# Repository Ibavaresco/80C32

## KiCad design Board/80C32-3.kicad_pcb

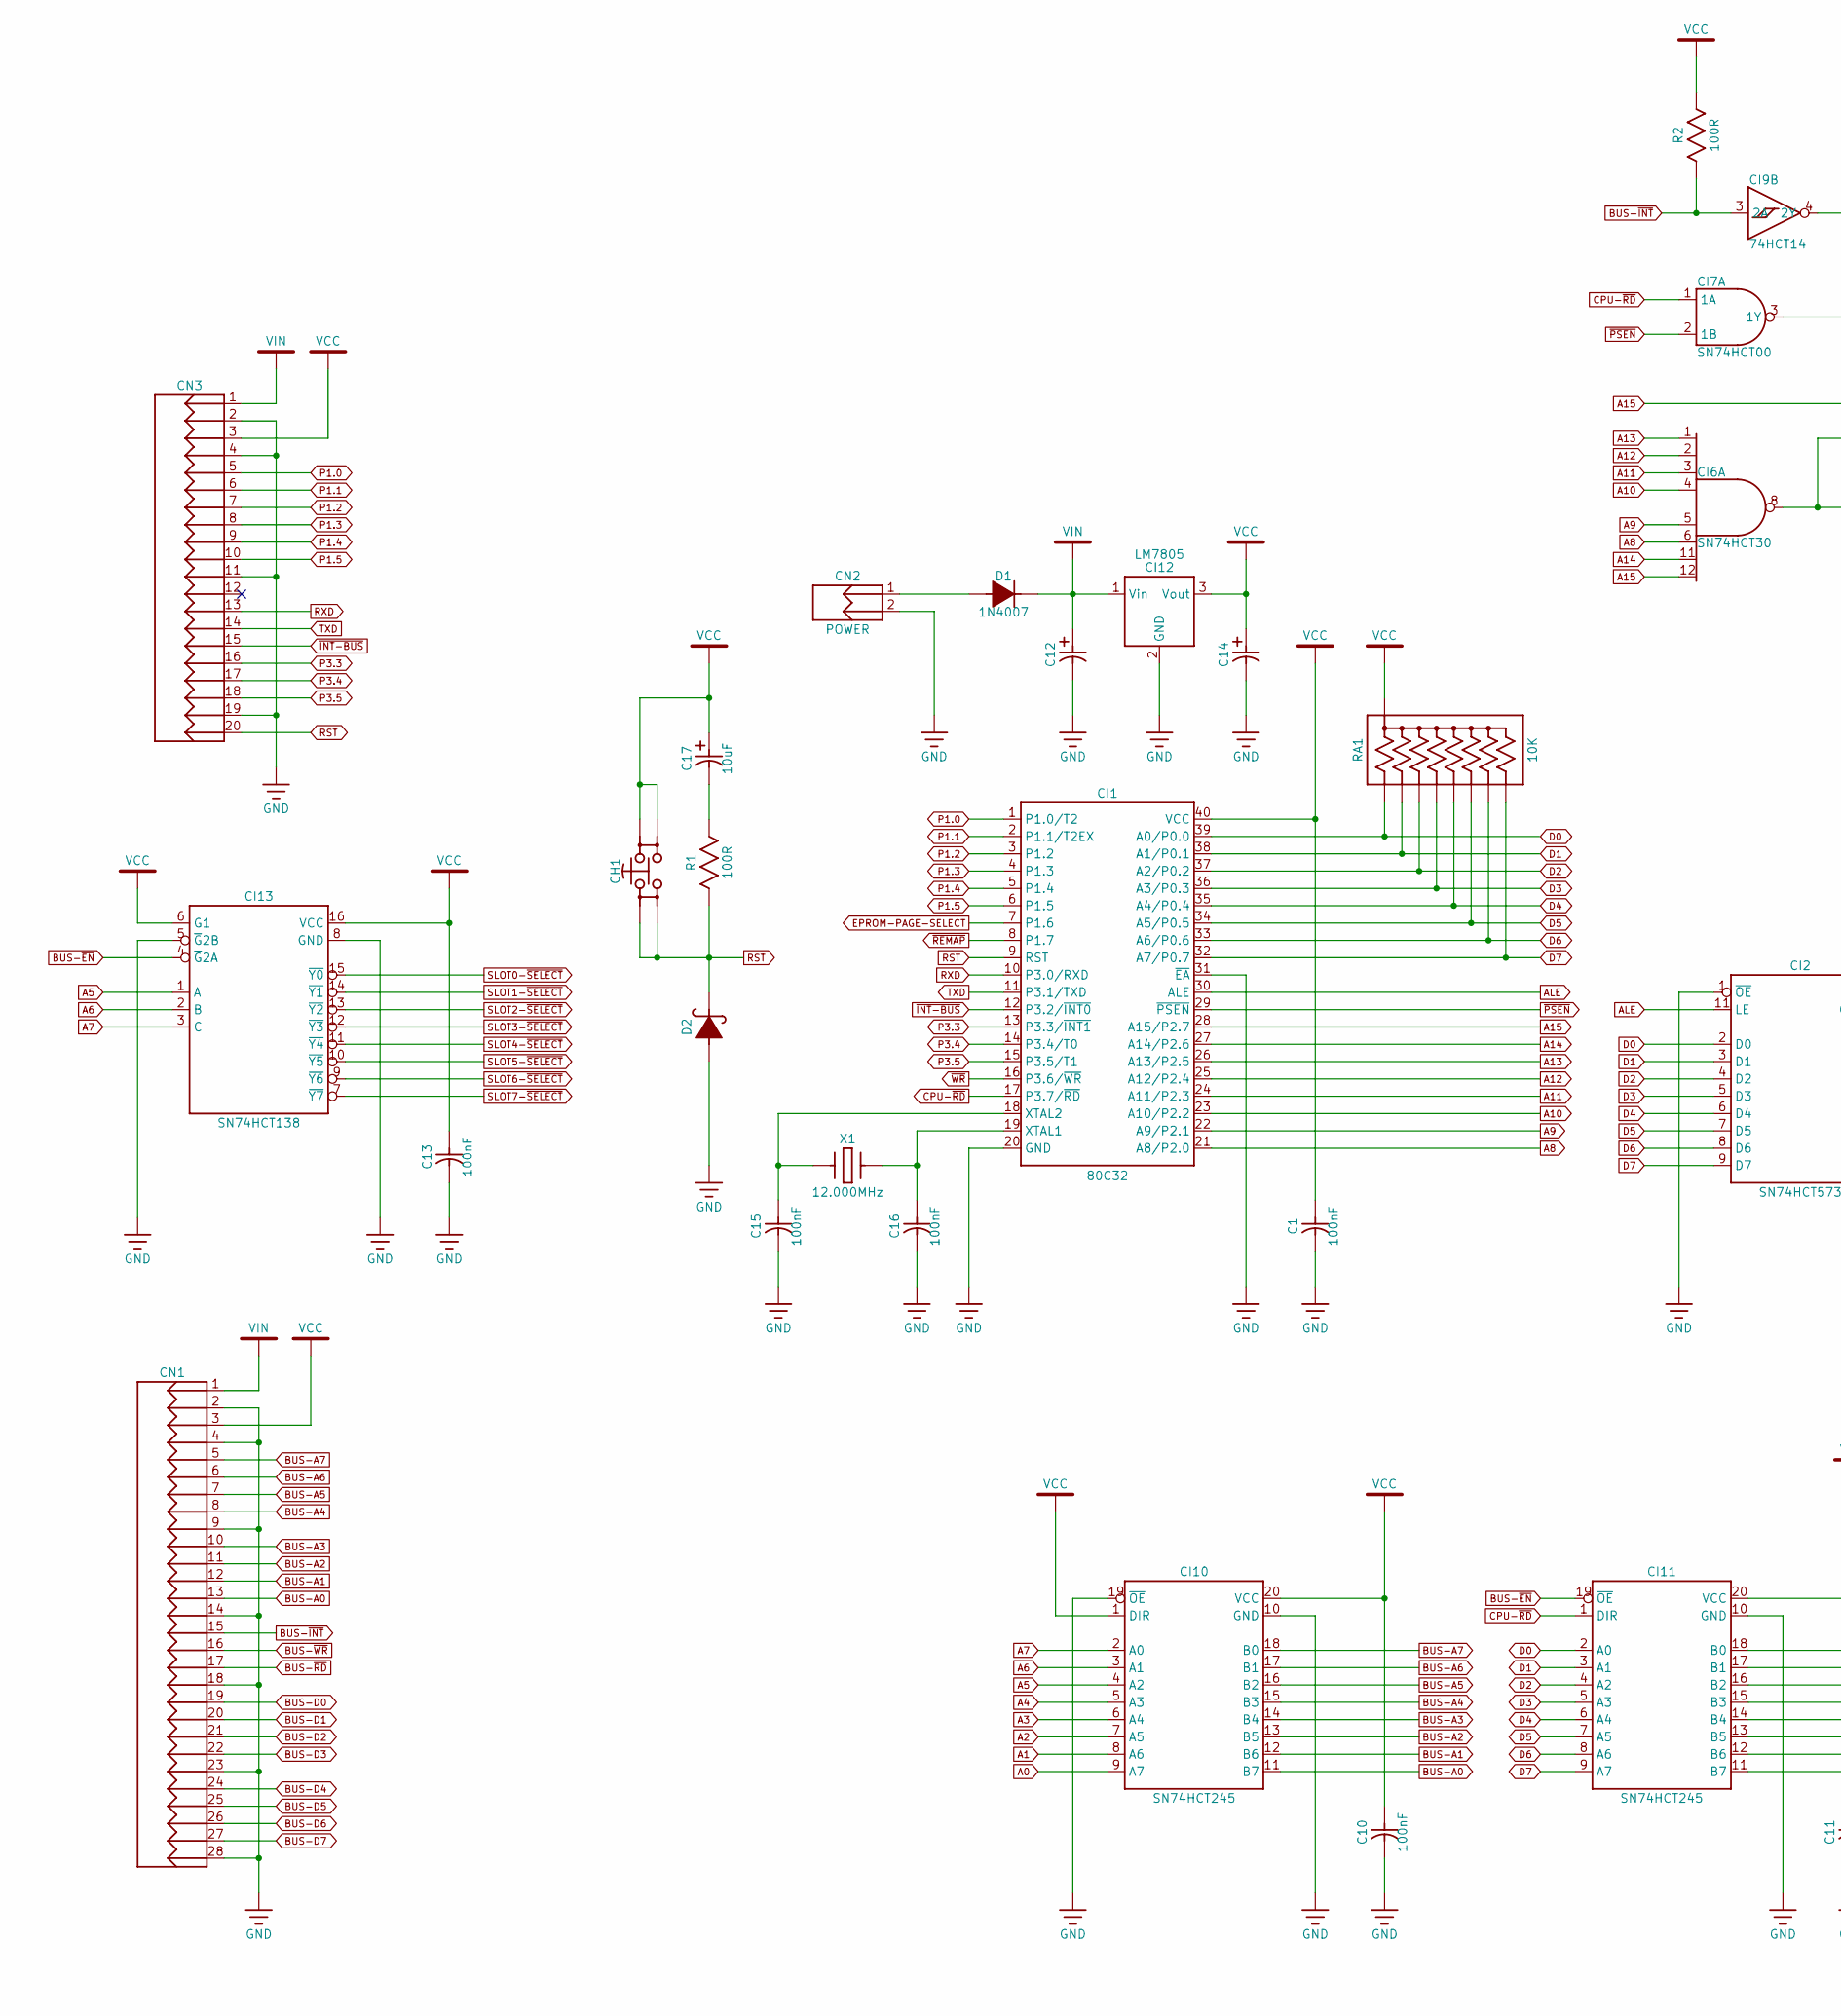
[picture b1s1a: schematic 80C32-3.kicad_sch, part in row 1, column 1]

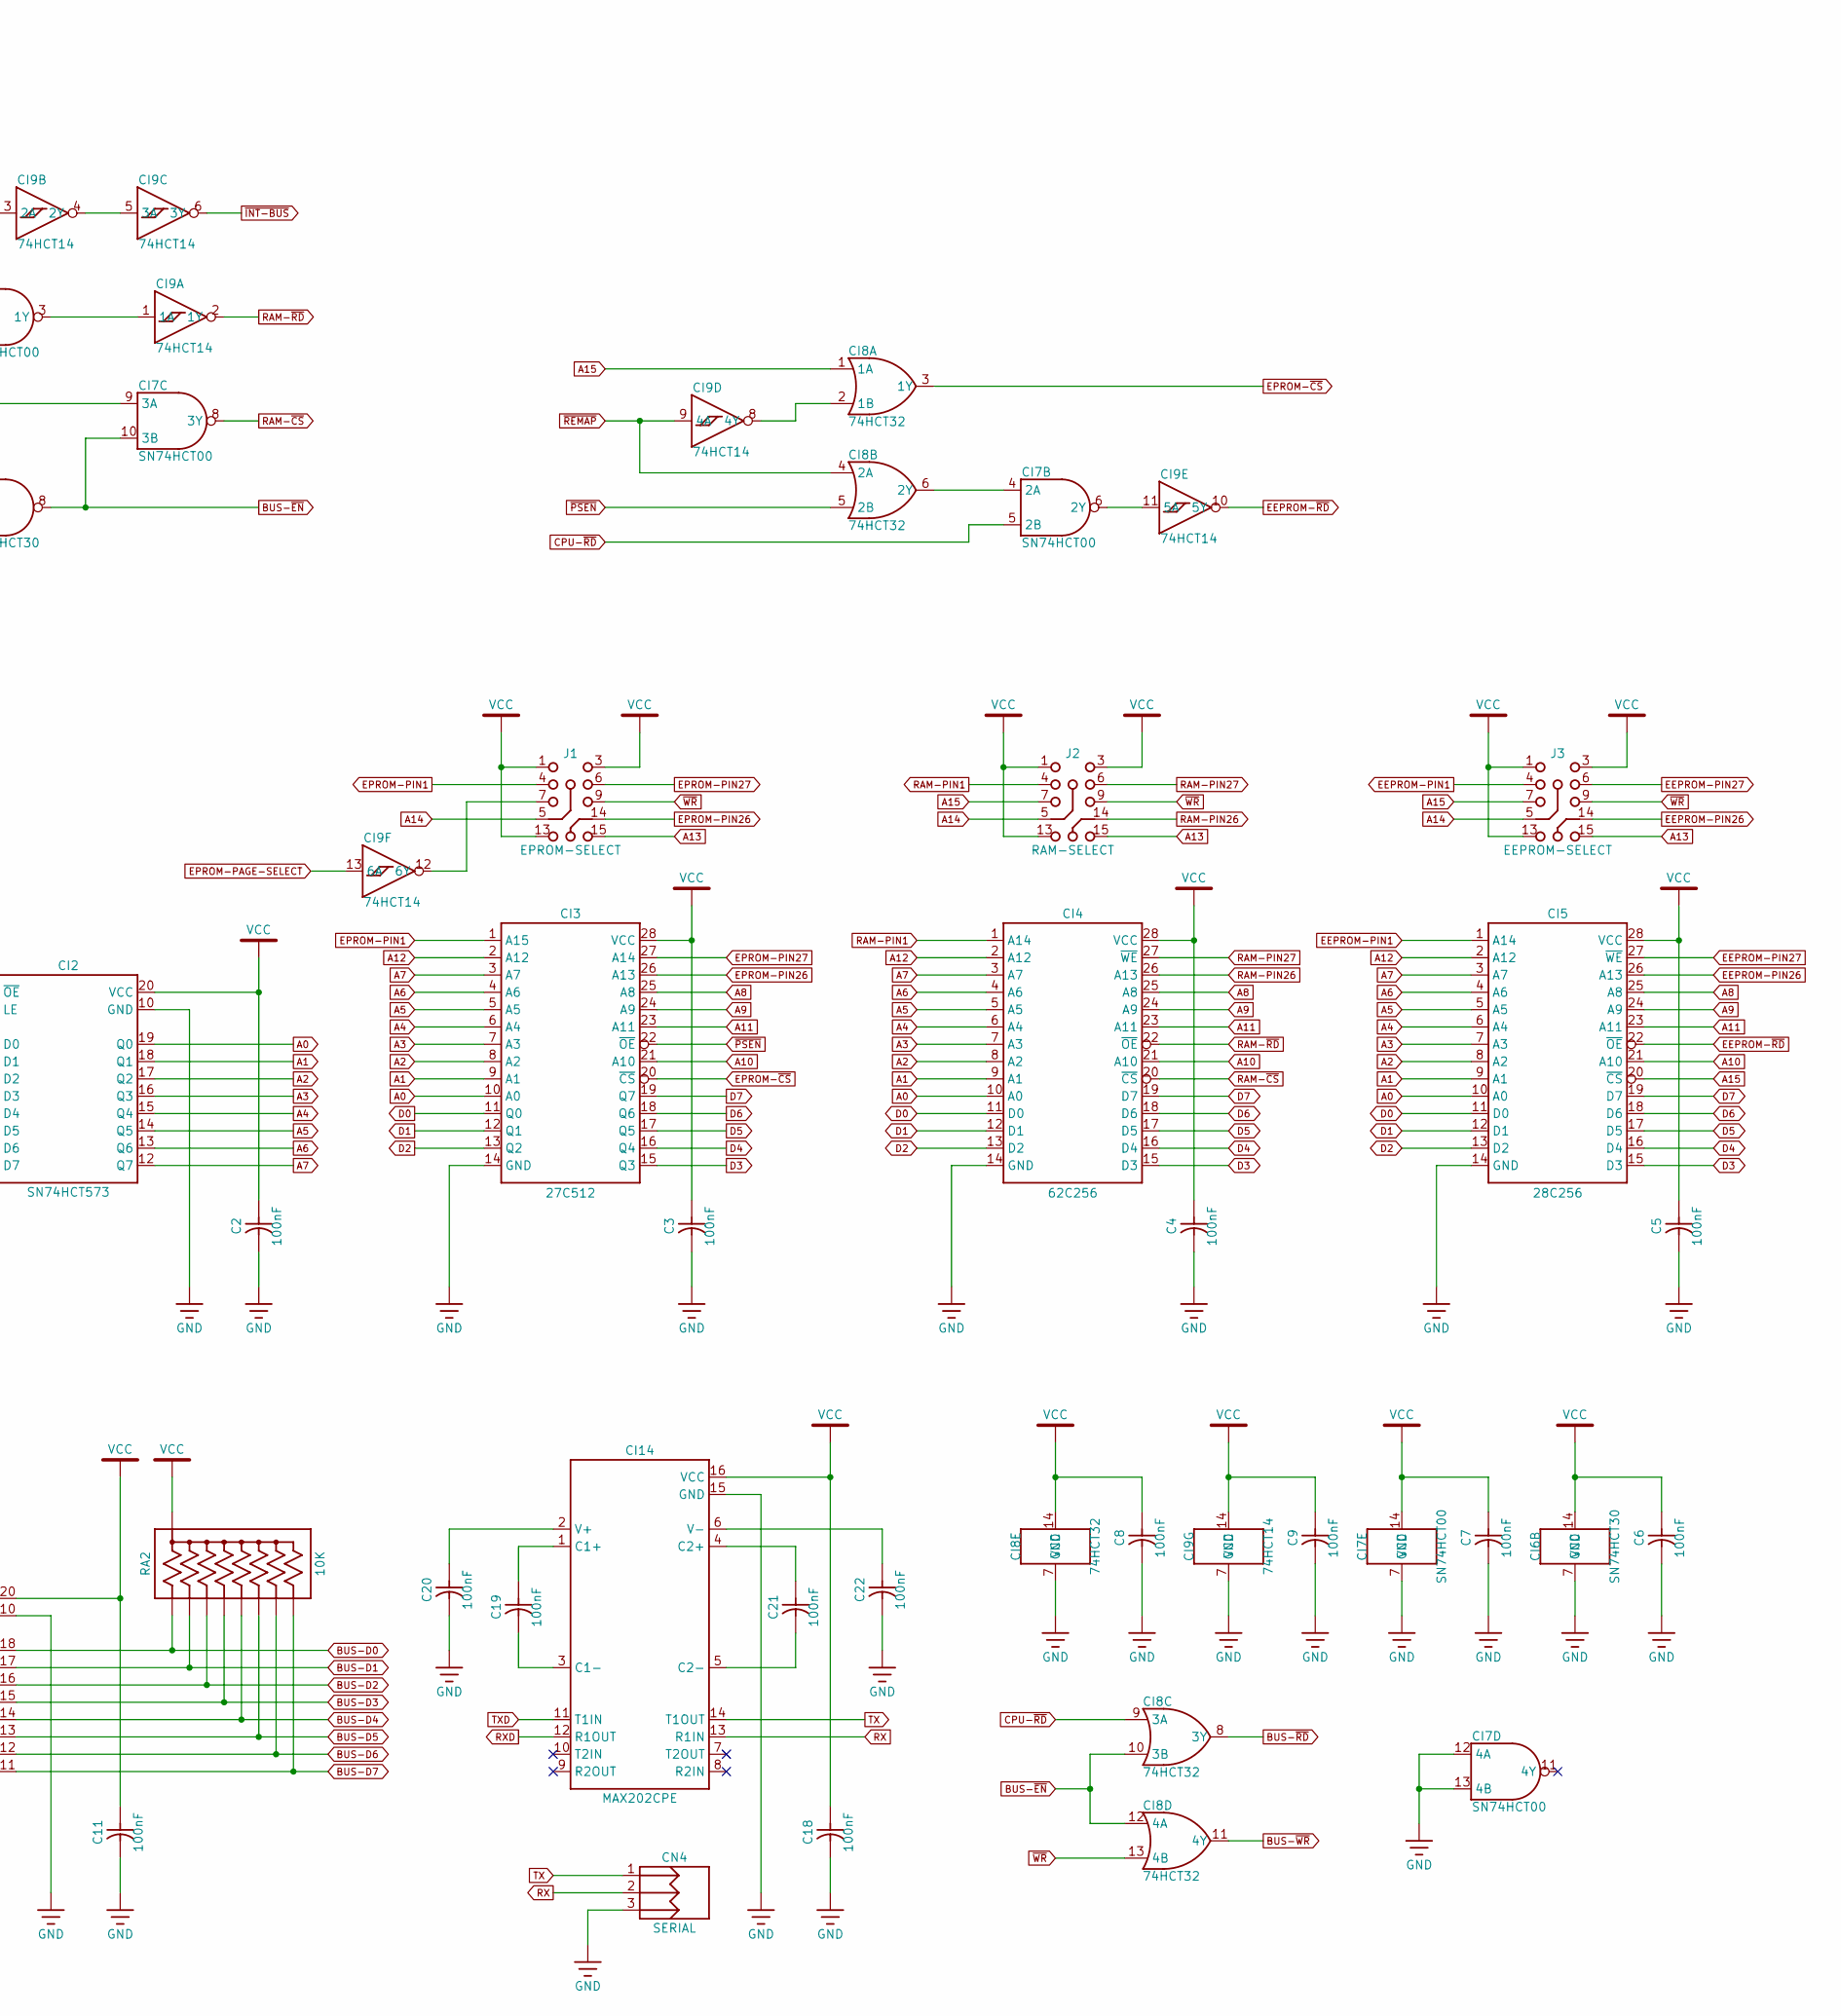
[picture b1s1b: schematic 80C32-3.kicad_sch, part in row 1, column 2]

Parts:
C1, C2, C3, C4, C5, C6, C7, C8, C9, C10, C11, C13, C15, C16, C18, C19, C20, C21, C22: 100nF; CAPACITOR-DISC-P5.08
C12, C14: CAPACITOR-RADIAL-D8.20-P3.8
C17: 10uF; CAPACITOR-RADIAL-D5.20-P2.5
CH1: SWITCH-TACTILE-MINI-VERTICAL
CI1: 80C32; DIP-40
CI2: SN74HCT573; DIP-20
CI3: 27C512; DIP-28
CI4: 62C256; DIP-28
CI5: 28C256; DIP-28
CI6: SN74HCT30; DIP-14
CI7: SN74HCT00; DIP-14
CI8: 74HCT32; DIP-14
CI9: 74HCT14; DIP-14
CI10, CI11: SN74HCT245; DIP-20
CI12: LM7805; TO-220AB
CI13: SN74HCT138; DIP-16
CI14: MAX202CPE; DIP-16
CN1: CONNECTOR-HEADER-1X28-P2.54
CN2: POWER; CONNECTOR-MOLEX-KK6373-02
CN3: CONNECTOR-HEADER-2X10-P2.54
CN4: SERIAL; CONNECTOR-MOLEX-KK6373-03
D1: 1N4007; DO-41
D2: DO-41
J1: EPROM-SELECT; JUMPER-H15
J2: RAM-SELECT; JUMPER-H15
J3: EEPROM-SELECT; JUMPER-H15
R1, R2: 100R; RESISTOR-CR25
RA1, RA2: 10K; SIP-9
X1: 12.000MHz; CRYSTAL-HC49-U

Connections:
A0: CI2.19 (Q0), CI3.10 (A0), CI4.10 (A0), CI5.10 (A0), CI10.9 (A7)
A1: CI2.18 (Q1), CI3.9 (A1), CI4.9 (A1), CI5.9 (A1), CI10.8 (A6)
A2: CI2.17 (Q2), CI3.8 (A2), CI4.8 (A2), CI5.8 (A2), CI10.7 (A5)
A3: CI2.16 (Q3), CI3.7 (A3), CI4.7 (A3), CI5.7 (A3), CI10.6 (A4)
A4: CI2.15 (Q4), CI3.6 (A4), CI4.6 (A4), CI5.6 (A4), CI10.5 (A3)
A5: CI2.14 (Q5), CI3.5 (A5), CI4.5 (A5), CI5.5 (A5), CI10.4 (A2), CI13.1 (A)
A6: CI2.13 (Q6), CI3.4 (A6), CI4.4 (A6), CI5.4 (A6), CI10.3 (A1), CI13.2 (B)
A7: CI2.12 (Q7), CI3.3 (A7), CI4.3 (A7), CI5.3 (A7), CI10.2 (A0), CI13.3 (C)
A8: CI1.21 (A8/P2.0), CI3.25 (A8), CI4.25 (A8), CI5.25 (A8), CI6.6
A9: CI1.22 (A9/P2.1), CI3.24 (A9), CI4.24 (A9), CI5.24 (A9), CI6.5
A10: CI1.23 (A10/P2.2), CI3.21 (A10), CI4.21 (A10), CI5.21 (A10), CI6.4
A11: CI1.24 (A11/P2.3), CI3.23 (A11), CI4.23 (A11), CI5.23 (A11), CI6.3
A12: CI1.25 (A12/P2.4), CI3.2 (A12), CI4.2 (A12), CI5.2 (A12), CI6.2
A13: CI1.26 (A13/P2.5), CI6.1, J1.15, J2.15, J3.15
A14: CI1.27 (A14/P2.6), CI6.11, J1.5, J2.5, J3.5
A15: CI1.28 (A15/P2.7), CI5.20 (~CS), CI6.12, CI7.9 (3A), CI8.1 (1A), J2.7, J3.7
ALE: CI1.30 (ALE), CI2.11 (LE)
BUS-A0: CI10.11 (B7), CN1.13
BUS-A1: CI10.12 (B6), CN1.12
BUS-A2: CI10.13 (B5), CN1.11
BUS-A3: CI10.14 (B4), CN1.10
BUS-A4: CI10.15 (B3), CN1.8
BUS-A5: CI10.16 (B2), CN1.7
BUS-A6: CI10.17 (B1), CN1.6
BUS-A7: CI10.18 (B0), CN1.5
BUS-D0: CI11.18 (B0), CN1.19, RA2.2 (R1)
BUS-D1: CI11.17 (B1), CN1.20, RA2.3 (R2)
BUS-D2: CI11.16 (B2), CN1.21, RA2.4 (R3)
BUS-D3: CI11.15 (B3), CN1.22, RA2.5 (R4)
BUS-D4: CI11.14 (B4), CN1.24, RA2.6 (R5)
BUS-D5: CI11.13 (B5), CN1.25, RA2.7 (R6)
BUS-D6: CI11.12 (B6), CN1.26, RA2.8 (R7)
BUS-D7: CI11.11 (B7), CN1.27, RA2.9 (R8)
BUS-~EN: CI6.8, CI7.10 (3B), CI8.10 (3B), CI8.12 (4A), CI11.19 (~OE), CI13.4 (~G2A)
BUS-~INT: CI9.3 (2A), CN1.15, R2.1
BUS-~RD: CI8.8 (3Y), CN1.17
BUS-~WR: CI8.11 (4Y), CN1.16
CPU-~RD: CI1.17 (P3.7/~RD), CI7.1 (1A), CI7.5 (2B), CI8.9 (3A), CI11.1 (DIR)
D0: CI1.39 (A0/P0.0), CI2.2 (D0), CI3.11 (Q0), CI4.11 (D0), CI5.11 (D0), CI11.2 (A0), RA1.2 (R1)
D1: CI1.38 (A1/P0.1), CI2.3 (D1), CI3.12 (Q1), CI4.12 (D1), CI5.12 (D1), CI11.3 (A1), RA1.3 (R2)
D2: CI1.37 (A2/P0.2), CI2.4 (D2), CI3.13 (Q2), CI4.13 (D2), CI5.13 (D2), CI11.4 (A2), RA1.4 (R3)
D3: CI1.36 (A3/P0.3), CI2.5 (D3), CI3.15 (Q3), CI4.15 (D3), CI5.15 (D3), CI11.5 (A3), RA1.5 (R4)
D4: CI1.35 (A4/P0.4), CI2.6 (D4), CI3.16 (Q4), CI4.16 (D4), CI5.16 (D4), CI11.6 (A4), RA1.6 (R5)
D5: CI1.34 (A5/P0.5), CI2.7 (D5), CI3.17 (Q5), CI4.17 (D5), CI5.17 (D5), CI11.7 (A5), RA1.7 (R6)
D6: CI1.33 (A6/P0.6), CI2.8 (D6), CI3.18 (Q6), CI4.18 (D6), CI5.18 (D6), CI11.8 (A6), RA1.8 (R7)
D7: CI1.32 (A7/P0.7), CI2.9 (D7), CI3.19 (Q7), CI4.19 (D7), CI5.19 (D7), CI11.9 (A7), RA1.9 (R8)
EEPROM-PIN1: CI5.1 (A14), J3.4
EEPROM-PIN26: CI5.26 (A13), J3.14
EEPROM-PIN27: CI5.27 (~WE), J3.6
EEPROM-~RD: CI5.22 (~OE), CI9.10 (5Y)
EPROM-PAGE-SELECT: CI1.7 (P1.6), CI9.13 (6A)
EPROM-PIN1: CI3.1 (A15), J1.4
EPROM-PIN26: CI3.26 (A13), J1.14
EPROM-PIN27: CI3.27 (A14), J1.6
EPROM-~CS: CI3.20 (~CS), CI8.3 (1Y)
GND: C1.2, C2.2, C3.2, C4.2, C5.2, C6.2, C7.2, C8.2, C9.2, C10.2, C11.2, C12.2 (-), C13.2, C14.2 (-), C15.2, C16.2, C18.2, C20.2, C22.2, CI1.20 (GND), CI1.31 (~EA), CI2.1 (~OE), CI2.10 (GND), CI3.14 (GND), CI4.14 (GND), CI5.14 (GND), CI6.7 (GND), CI7.7 (GND), CI7.12 (4A), CI7.13 (4B), CI8.7 (GND), CI9.7 (GND), CI10.10 (GND), CI10.19 (~OE), CI11.10 (GND), CI12.2 (GND), CI13.5 (~G2B), CI13.8 (GND), CI14.15 (GND), CN1.2, CN1.4, CN1.9, CN1.14, CN1.18, CN1.23, CN1.28, CN2.2, CN3.2, CN3.4, CN3.11, CN3.19, CN4.3, D2.1 (A)
unnamed: C17.2 (-), R1.2
unnamed: C16.1, CI1.19 (XTAL1), X1.2
unnamed: C15.1, CI1.18 (XTAL2), X1.1
unnamed: CI7.3 (1Y), CI9.1 (1A)
unnamed: CI7.4 (2A), CI8.6 (2Y)
unnamed: CI7.6 (2Y), CI9.11 (5A)
unnamed: CI8.2 (1B), CI9.8 (4Y)
unnamed: CI9.4 (2Y), CI9.5 (3A)
unnamed: CI9.12 (6Y), J1.7
unnamed: C19.1, CI14.1 (C1+)
unnamed: C19.2, CI14.3 (C1-)
unnamed: C21.1, CI14.4 (C2+)
unnamed: C21.2, CI14.5 (C2-)
unnamed: C20.1, CI14.2 (V+)
unnamed: C22.1, CI14.6 (V-)
unnamed: CN2.1, D1.1 (A)
P1.0: CI1.1 (P1.0/T2), CN3.5
P1.1: CI1.2 (P1.1/T2EX), CN3.6
P1.2: CI1.3 (P1.2), CN3.7
P1.3: CI1.4 (P1.3), CN3.8
P1.4: CI1.5 (P1.4), CN3.9
P1.5: CI1.6 (P1.5), CN3.10
P3.3: CI1.13 (P3.3/~INT1), CN3.16
P3.4: CI1.14 (P3.4/T0), CN3.17
P3.5: CI1.15 (P3.5/T1), CN3.18
RAM-PIN1: CI4.1 (A14), J2.4
RAM-PIN26: CI4.26 (A13), J2.14
RAM-PIN27: CI4.27 (~WE), J2.6
RAM-~CS: CI4.20 (~CS), CI7.8 (3Y)
RAM-~RD: CI4.22 (~OE), CI9.2 (1Y)
RST: CH1.1, CH1.2, CI1.9 (RST), CN3.20, D2.2 (K), R1.1
RX: CI14.13 (R1IN), CN4.2
RXD: CI1.10 (P3.0/RXD), CI14.12 (R1OUT), CN3.13
TX: CI14.14 (T1OUT), CN4.1
TXD: CI1.11 (P3.1/TXD), CI14.11 (T1IN), CN3.14
VCC: C1.1, C2.1, C3.1, C4.1, C5.1, C6.1, C7.1, C8.1, C9.1, C10.1, C11.1, C13.1, C14.1 (+), C17.1 (+), C18.1, CH1.3, CH1.4, CI1.40 (VCC), CI2.20 (VCC), CI3.28 (VCC), CI4.28 (VCC), CI5.28 (VCC), CI6.14 (VCC), CI7.14 (VCC), CI8.14 (VCC), CI9.14 (VCC), CI10.1 (DIR), CI10.20 (VCC), CI11.20 (VCC), CI12.3 (Vout), CI13.6 (G1), CI13.16 (VCC), CI14.16 (VCC), CN1.3, CN3.3, J1.1, J1.3, J1.13, J2.1, J2.3, J2.13, J3.1, J3.3, J3.13, R2.2, RA1.1 (COMMON), RA2.1 (COMMON)
VIN: C12.1 (+), CI12.1 (Vin), CN1.1, CN3.1, D1.2 (K)
~INT-BUS: CI1.12 (P3.2/~INT0), CI9.6 (3Y), CN3.15
~PSEN: CI1.29 (~PSEN), CI3.22 (~OE), CI7.2 (1B), CI8.5 (2B)
~REMAP: CI1.8 (P1.7), CI8.4 (2A), CI9.9 (4A)
~WR: CI1.16 (P3.6/~WR), CI8.13 (4B), J1.9, J2.9, J3.9

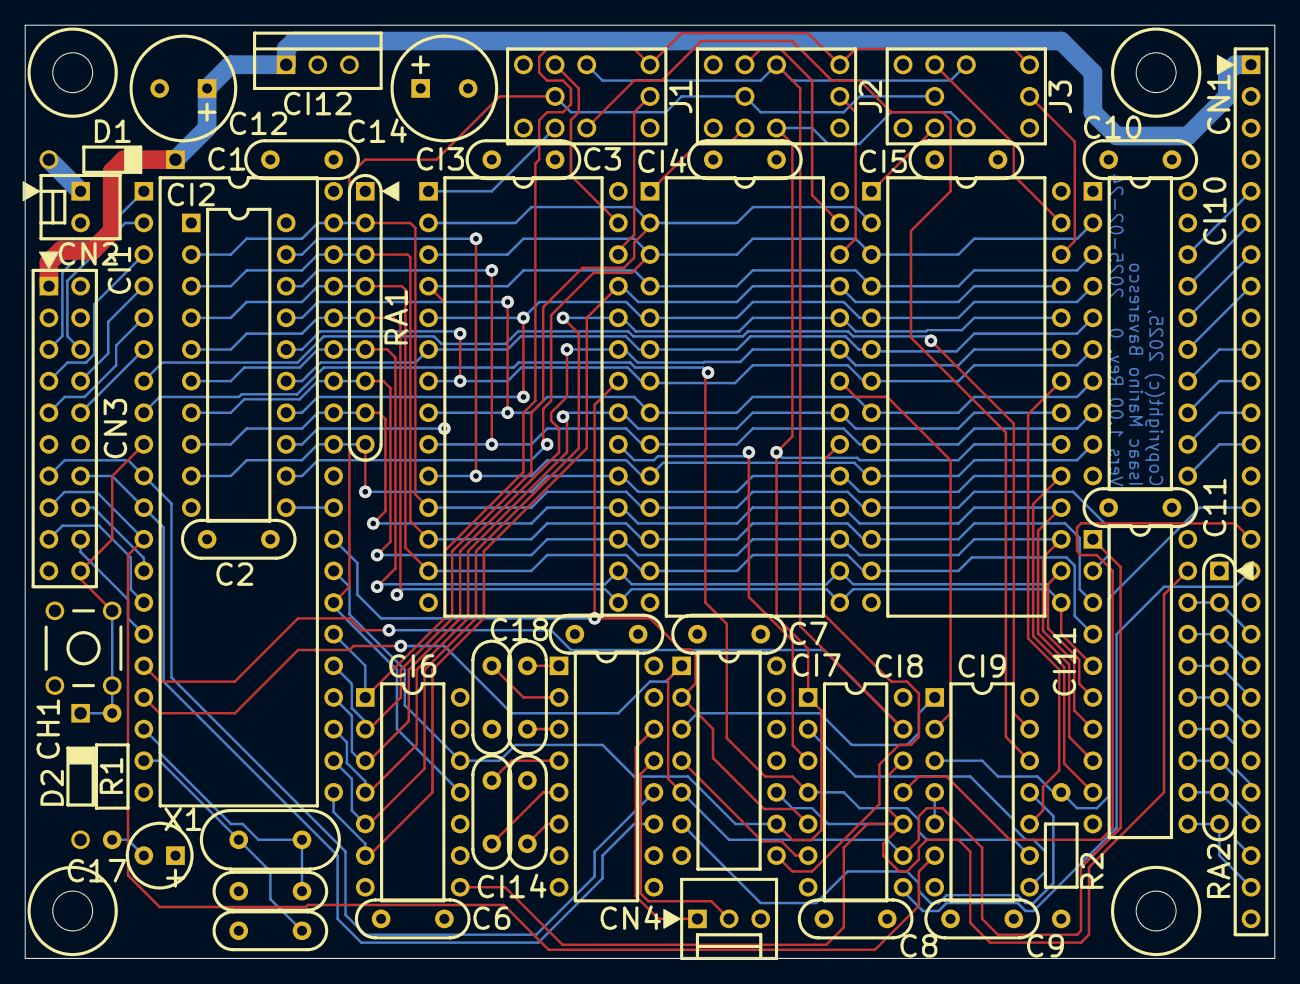
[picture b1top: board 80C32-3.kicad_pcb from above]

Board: 4 copper layers, 100.3 x 74.9 mm, 49 parts (0 on the bottom side), 97 nets.

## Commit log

2026-03-05 First commit.
2026-03-05 - Corrected value of the crystal load capacitors. - Added note stating that CI13 is not implemented in this version of the board. - Added missing 3D model.
2026-03-08 Added documentation about how to connect LCD and keypad.
2026-03-10 Added PDF files with the schematics.

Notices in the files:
Board/80C32-3.kicad_pcb:
Copyright(c) 2025,
Isaac Marino Bavaresco
